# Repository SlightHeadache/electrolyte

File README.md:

# Electrolyte 10x4 Ortholinear Keyboard PCB

Originally by @rlbaxter. Modified by me to better support the Umō case.

## Firmware

- [QMK](https://github.com/rlbaxter/qmk_firmware/tree/rlbaxter/keyboards/electrolyte)
- [ZMK](https://github.com/rlbaxter/zmk/tree/electrolyte/app/boards/shields/electrolyte)

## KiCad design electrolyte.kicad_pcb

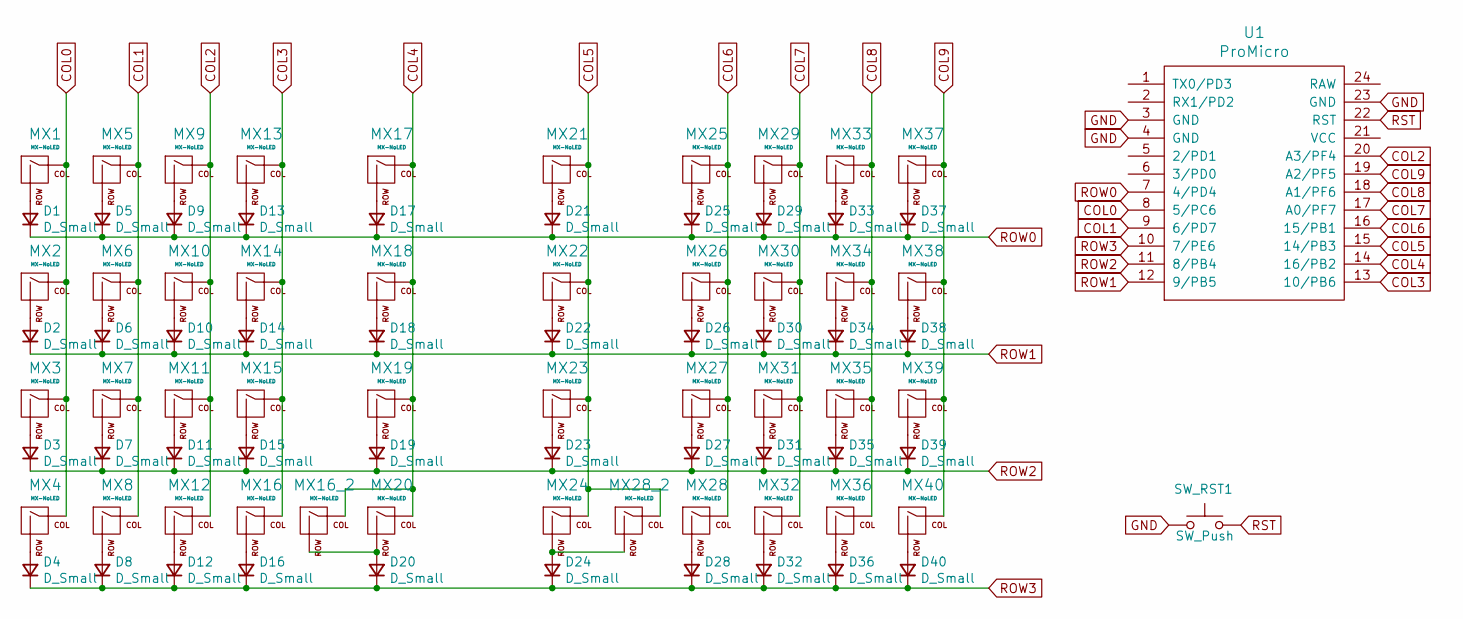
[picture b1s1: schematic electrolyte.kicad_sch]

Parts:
D1, D2, D3, D4, D5, D6, D7, D8, D9, D10, D11, D12, D13, D14, D15, D16, D17, D18, D19, D20, D21, D22, D23, D24, D25, D26, D27, D28, D29, D30, D31, D32, D33, D34, D35, D36, D37, D38, D39, D40: D_Small; Diode-Hybrid-Back
MX1, MX2, MX3, MX4, MX5, MX6, MX7, MX8, MX9, MX10, MX11, MX12, MX13, MX14, MX15, MX16, MX17, MX18, MX19, MX20, MX21, MX22, MX23, MX24, MX25, MX26, MX27, MX28, MX29, MX30, MX31, MX32, MX33, MX34, MX35, MX36, MX37, MX38, MX39, MX40: MX-NoLED; MXOnly-1U-NoLED
MX16_2, MX28_2: MX-NoLED; SW_Cherry_MX_2.00u_PCB
SW_RST1: SW_Push; SW_SPST_TL3342
U1: ProMicro; ArduinoProMicro

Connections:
COL0: MX1.1 (COL), MX2.1 (COL), MX3.1 (COL), MX4.1 (COL), U1.8 (5/PC6)
COL1: MX5.1 (COL), MX6.1 (COL), MX7.1 (COL), MX8.1 (COL), U1.9 (6/PD7)
COL2: MX9.1 (COL), MX10.1 (COL), MX11.1 (COL), MX12.1 (COL), U1.20 (A3/PF4)
COL3: MX13.1 (COL), MX14.1 (COL), MX15.1 (COL), MX16.1 (COL), U1.13 (10/PB6)
COL4: MX16_2.1 (COL), MX17.1 (COL), MX18.1 (COL), MX19.1 (COL), MX20.1 (COL), U1.14 (16/PB2)
COL5: MX21.1 (COL), MX22.1 (COL), MX23.1 (COL), MX24.1 (COL), MX28_2.1 (COL), U1.15 (14/PB3)
COL6: MX25.1 (COL), MX26.1 (COL), MX27.1 (COL), MX28.1 (COL), U1.16 (15/PB1)
COL7: MX29.1 (COL), MX30.1 (COL), MX31.1 (COL), MX32.1 (COL), U1.17 (A0/PF7)
COL8: MX33.1 (COL), MX34.1 (COL), MX35.1 (COL), MX36.1 (COL), U1.18 (A1/PF6)
COL9: MX37.1 (COL), MX38.1 (COL), MX39.1 (COL), MX40.1 (COL), U1.19 (A2/PF5)
GND: SW_RST1.1, U1.3 (GND), U1.4 (GND), U1.23 (GND)
unnamed: D1.2 (A), MX1.2 (ROW)
unnamed: D2.2 (A), MX2.2 (ROW)
unnamed: D3.2 (A), MX3.2 (ROW)
unnamed: D4.2 (A), MX4.2 (ROW)
unnamed: D5.2 (A), MX5.2 (ROW)
unnamed: D6.2 (A), MX6.2 (ROW)
unnamed: D7.2 (A), MX7.2 (ROW)
unnamed: D8.2 (A), MX8.2 (ROW)
unnamed: D9.2 (A), MX9.2 (ROW)
unnamed: D10.2 (A), MX10.2 (ROW)
unnamed: D11.2 (A), MX11.2 (ROW)
unnamed: D12.2 (A), MX12.2 (ROW)
unnamed: D13.2 (A), MX13.2 (ROW)
unnamed: D14.2 (A), MX14.2 (ROW)
unnamed: D15.2 (A), MX15.2 (ROW)
unnamed: D16.2 (A), MX16.2 (ROW)
unnamed: D17.2 (A), MX17.2 (ROW)
unnamed: D18.2 (A), MX18.2 (ROW)
unnamed: D19.2 (A), MX19.2 (ROW)
unnamed: D20.2 (A), MX16_2.2 (ROW), MX20.2 (ROW)
unnamed: D21.2 (A), MX21.2 (ROW)
unnamed: D22.2 (A), MX22.2 (ROW)
unnamed: D23.2 (A), MX23.2 (ROW)
unnamed: D24.2 (A), MX24.2 (ROW), MX28_2.2 (ROW)
unnamed: D25.2 (A), MX25.2 (ROW)
unnamed: D26.2 (A), MX26.2 (ROW)
unnamed: D27.2 (A), MX27.2 (ROW)
unnamed: D28.2 (A), MX28.2 (ROW)
unnamed: D29.2 (A), MX29.2 (ROW)
unnamed: D30.2 (A), MX30.2 (ROW)
unnamed: D31.2 (A), MX31.2 (ROW)
unnamed: D32.2 (A), MX32.2 (ROW)
unnamed: D33.2 (A), MX33.2 (ROW)
unnamed: D34.2 (A), MX34.2 (ROW)
unnamed: D35.2 (A), MX35.2 (ROW)
unnamed: D36.2 (A), MX36.2 (ROW)
unnamed: D37.2 (A), MX37.2 (ROW)
unnamed: D38.2 (A), MX38.2 (ROW)
unnamed: D39.2 (A), MX39.2 (ROW)
unnamed: D40.2 (A), MX40.2 (ROW)
ROW0: D1.1 (K), D5.1 (K), D9.1 (K), D13.1 (K), D17.1 (K), D21.1 (K), D25.1 (K), D29.1 (K), D33.1 (K), D37.1 (K), U1.7 (4/PD4)
ROW1: D2.1 (K), D6.1 (K), D10.1 (K), D14.1 (K), D18.1 (K), D22.1 (K), D26.1 (K), D30.1 (K), D34.1 (K), D38.1 (K), U1.12 (9/PB5)
ROW2: D3.1 (K), D7.1 (K), D11.1 (K), D15.1 (K), D19.1 (K), D23.1 (K), D27.1 (K), D31.1 (K), D35.1 (K), D39.1 (K), U1.11 (8/PB4)
ROW3: D4.1 (K), D8.1 (K), D12.1 (K), D16.1 (K), D20.1 (K), D24.1 (K), D28.1 (K), D32.1 (K), D36.1 (K), D40.1 (K), U1.10 (7/PE6)
RST: SW_RST1.2, U1.22 (RST)

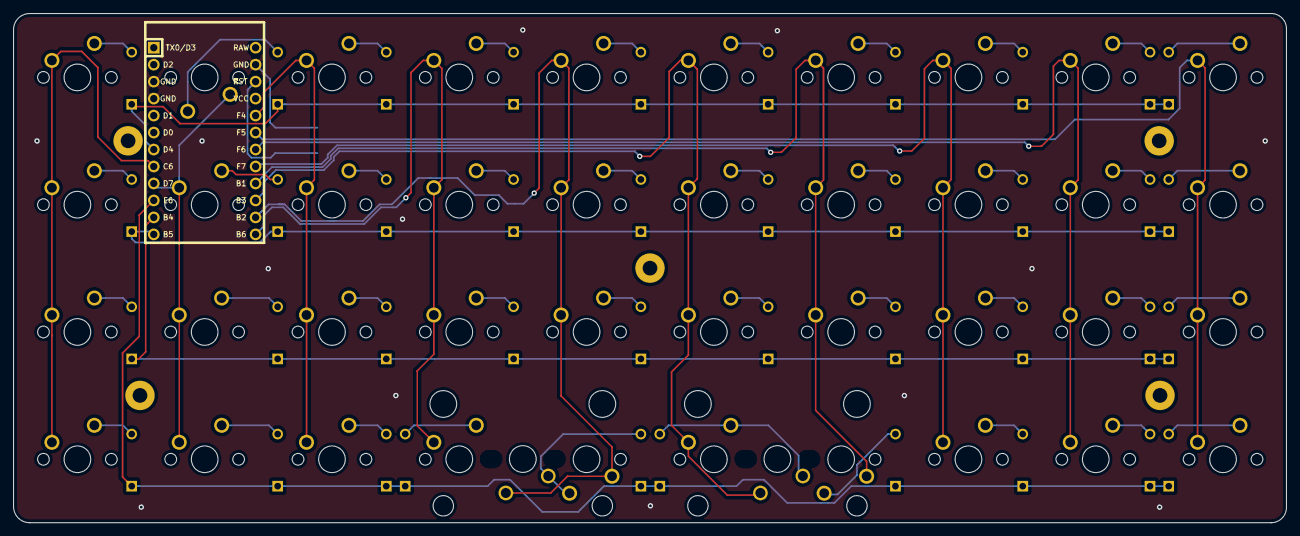
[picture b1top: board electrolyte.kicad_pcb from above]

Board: 2 copper layers, 190.5 x 76.2 mm, 85 parts (1 on the bottom side), 56 nets.

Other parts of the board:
x_x: MountingHole_2.2mm_M2_Pad

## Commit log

2023-02-08 create a modified repo
2023-02-08 update license
